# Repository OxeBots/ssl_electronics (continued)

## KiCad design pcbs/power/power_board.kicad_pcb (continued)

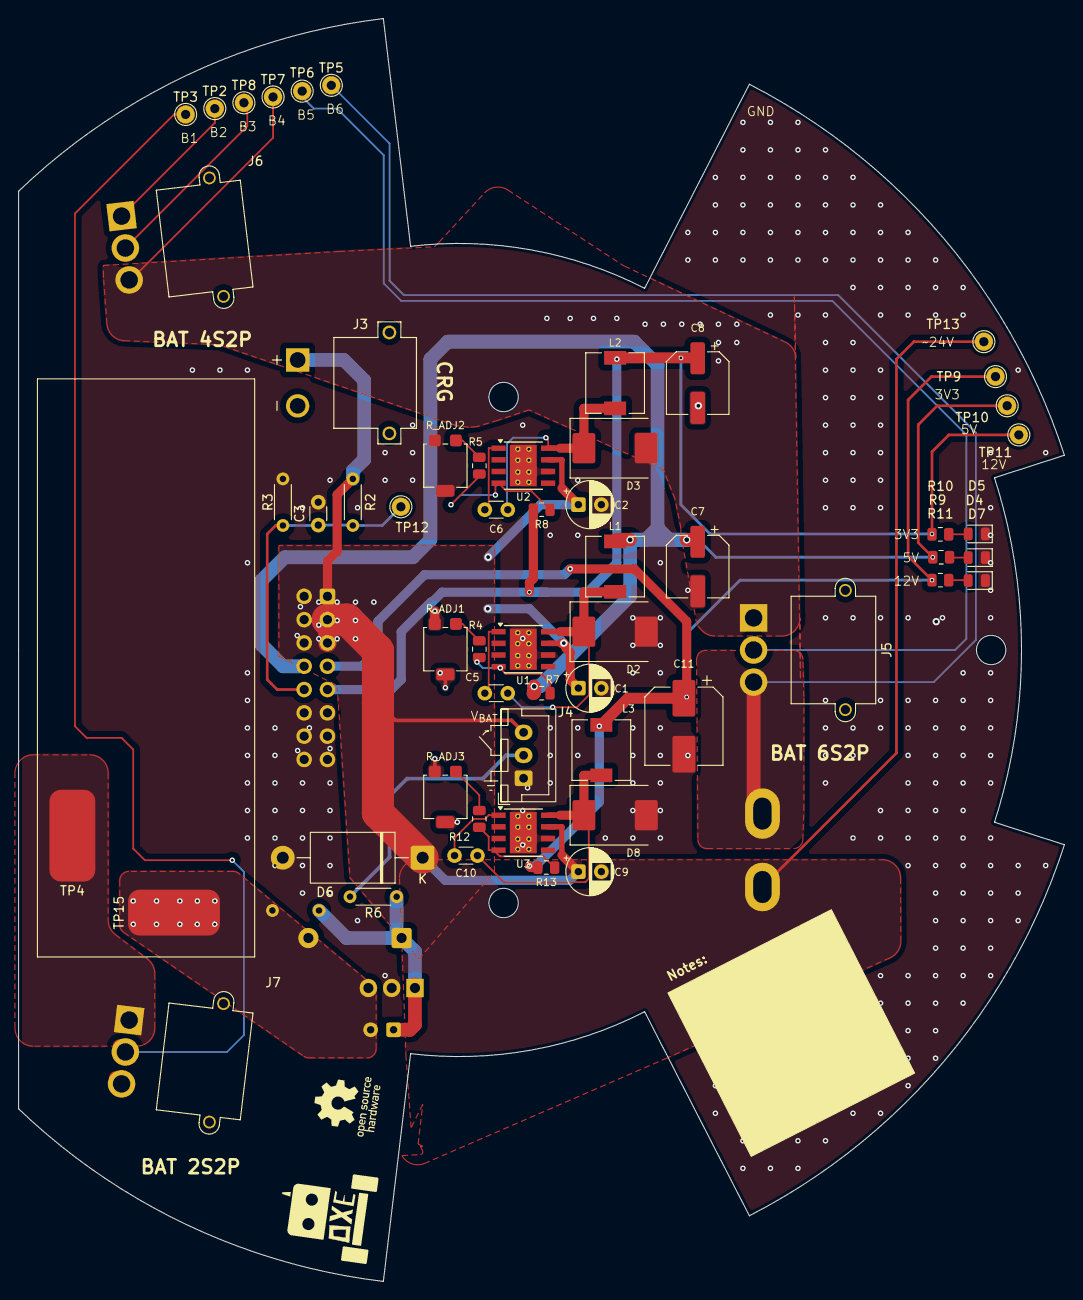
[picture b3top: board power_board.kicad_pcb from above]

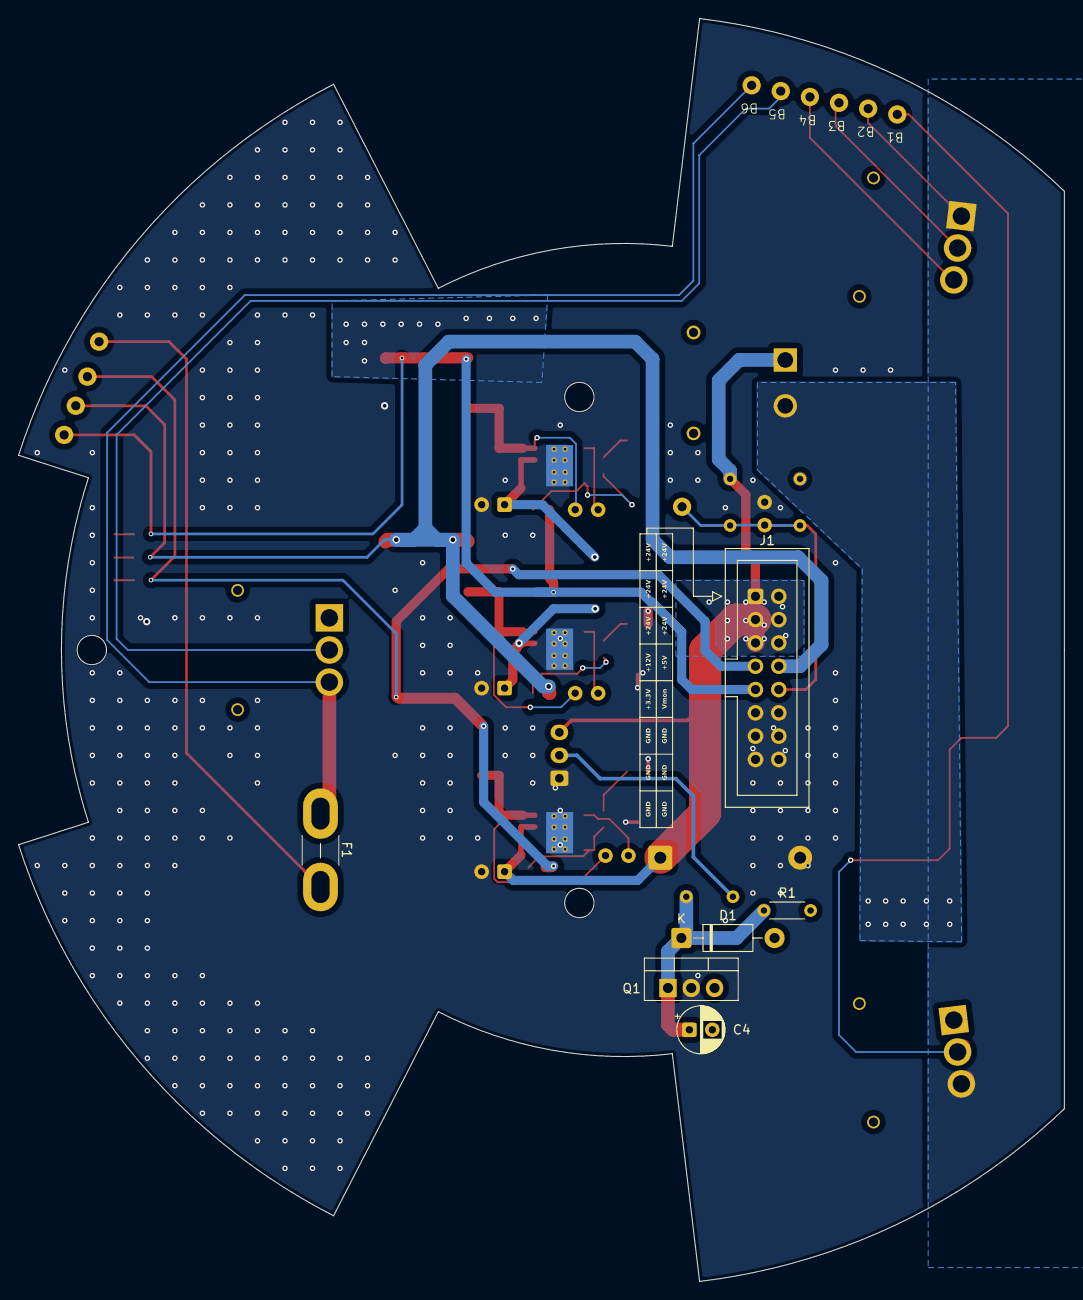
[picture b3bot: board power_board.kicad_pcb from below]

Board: 2 copper layers, 114.0 x 137.6 mm, 65 parts (6 on the bottom side), 31 nets.

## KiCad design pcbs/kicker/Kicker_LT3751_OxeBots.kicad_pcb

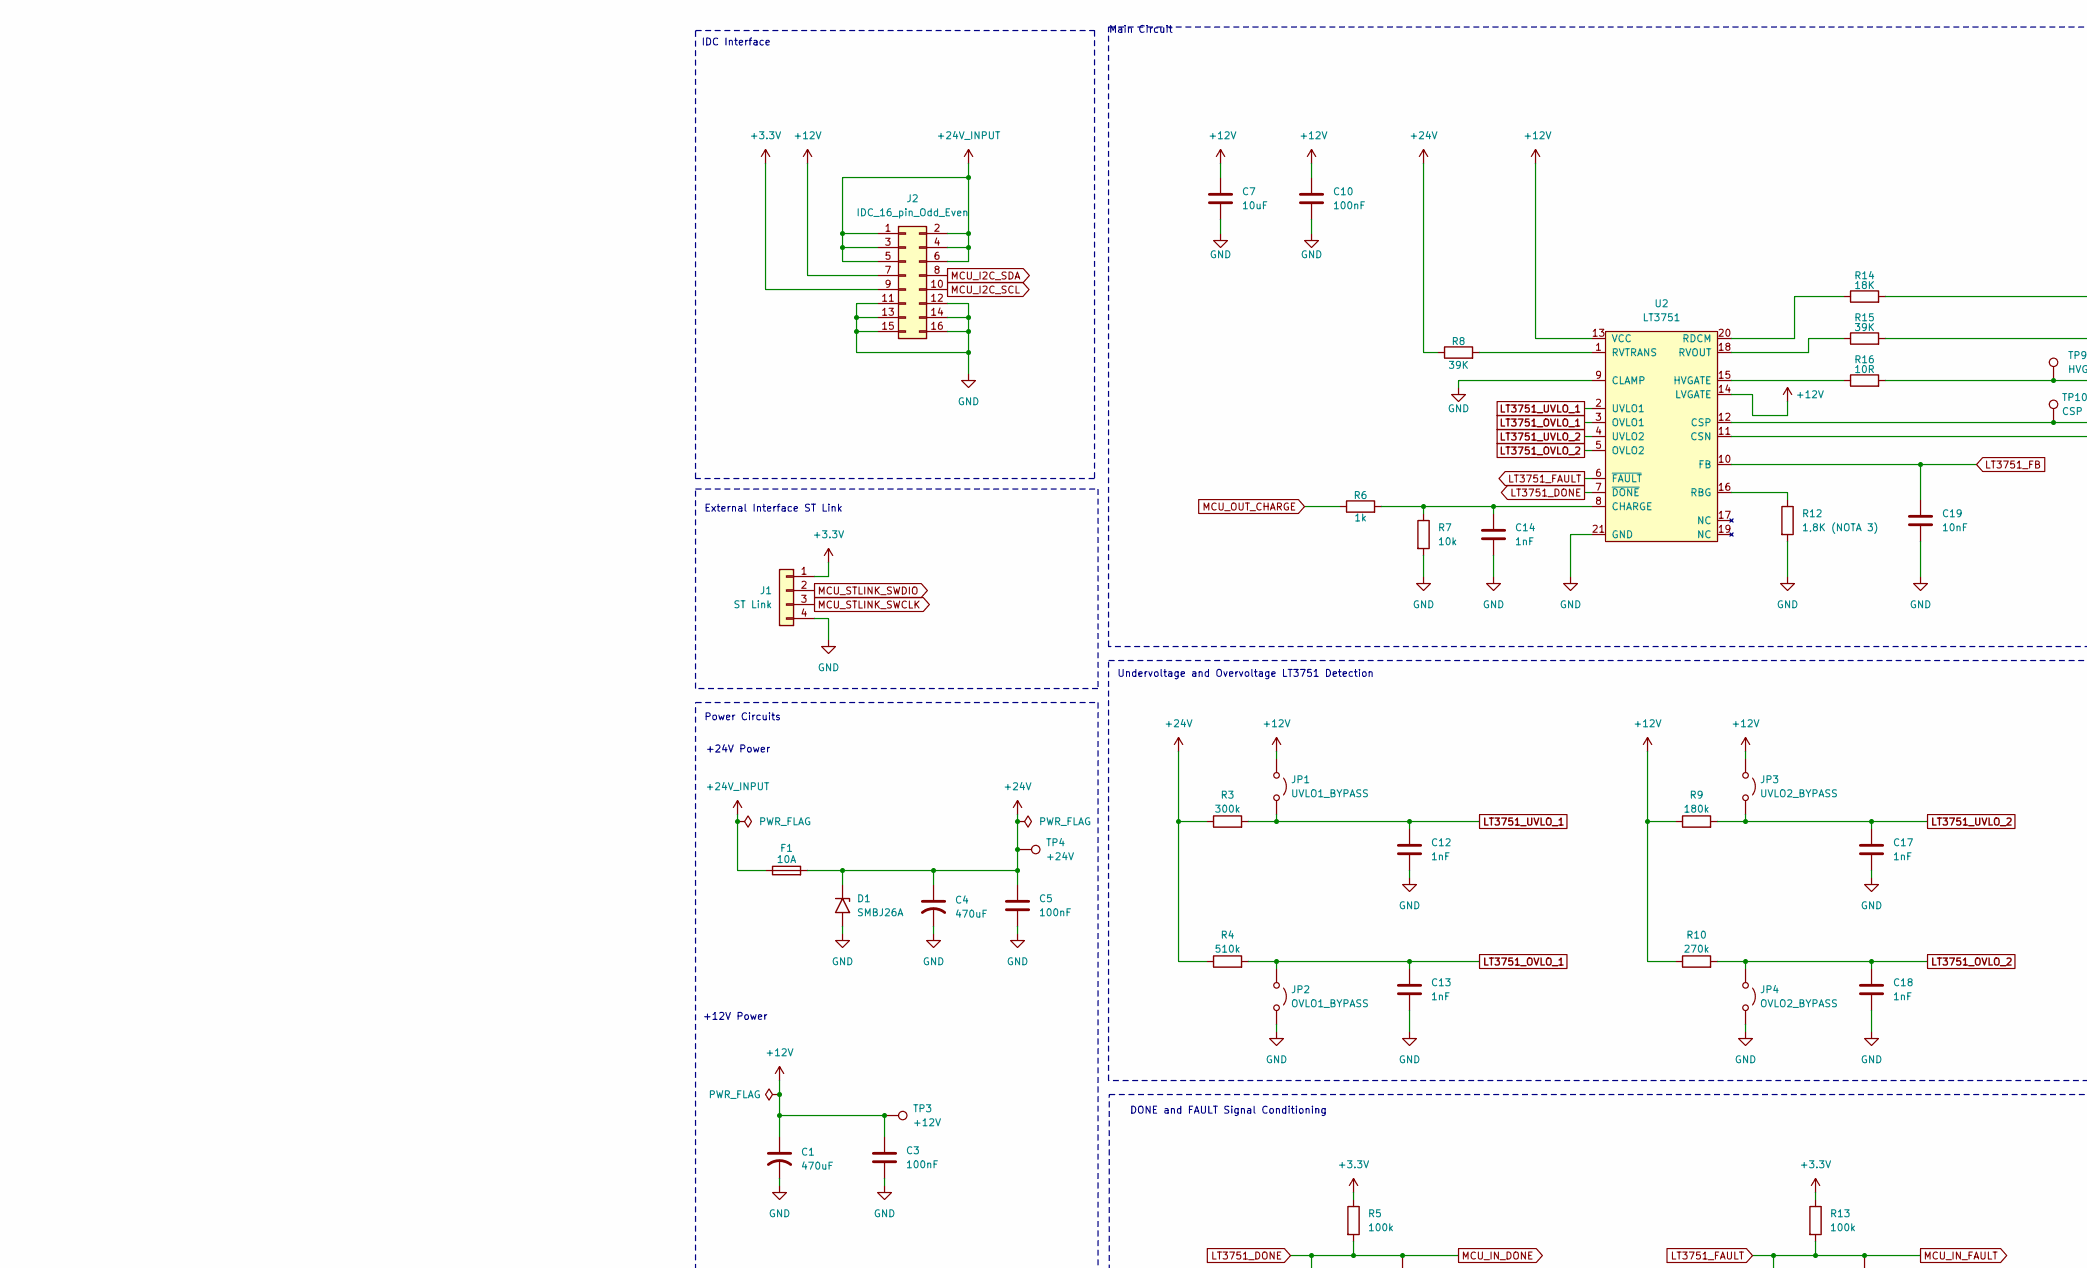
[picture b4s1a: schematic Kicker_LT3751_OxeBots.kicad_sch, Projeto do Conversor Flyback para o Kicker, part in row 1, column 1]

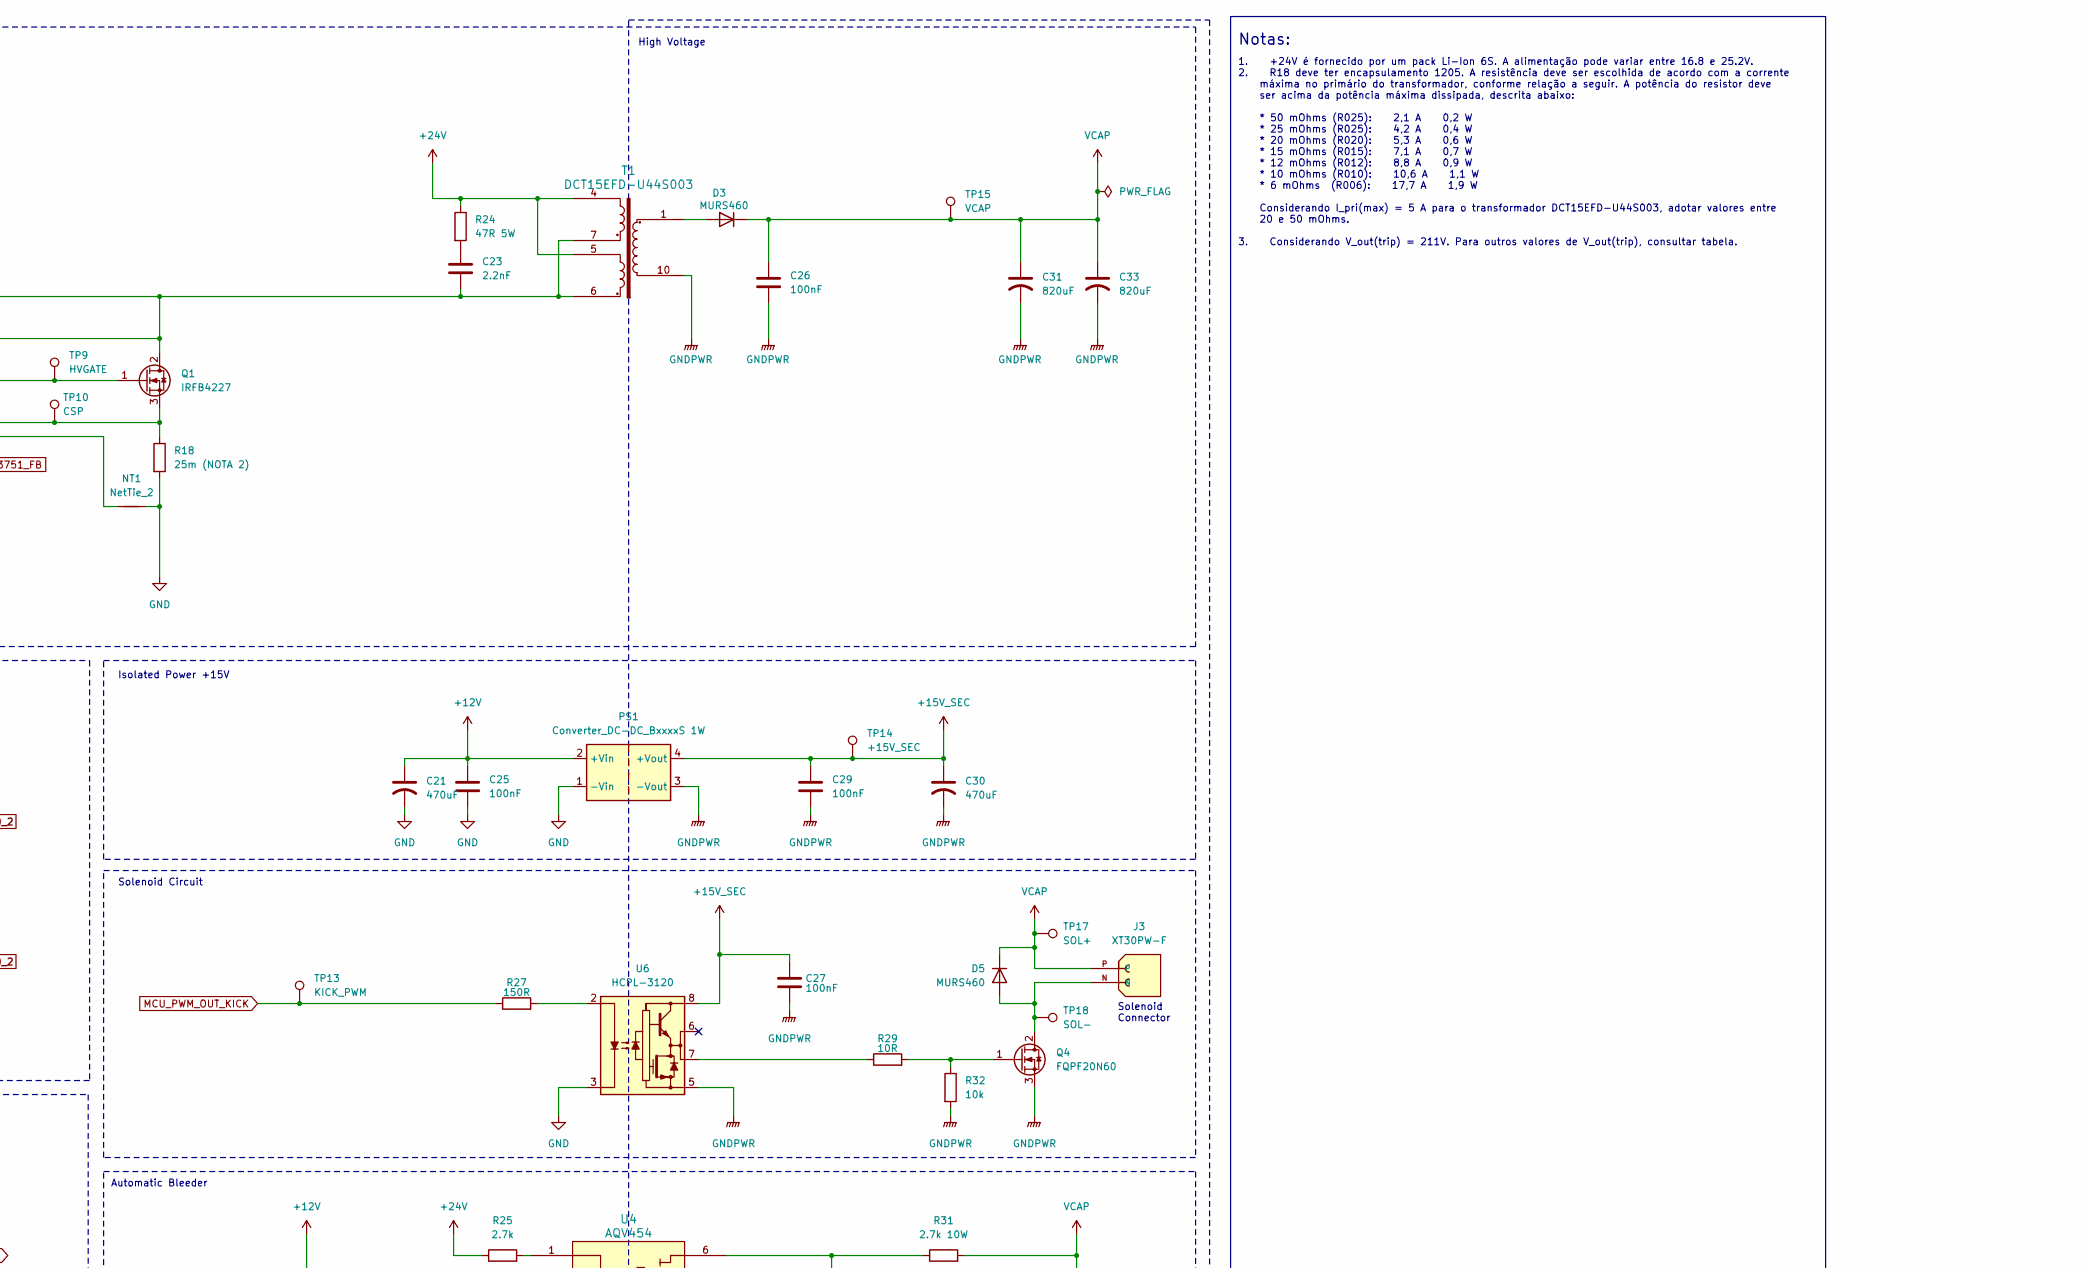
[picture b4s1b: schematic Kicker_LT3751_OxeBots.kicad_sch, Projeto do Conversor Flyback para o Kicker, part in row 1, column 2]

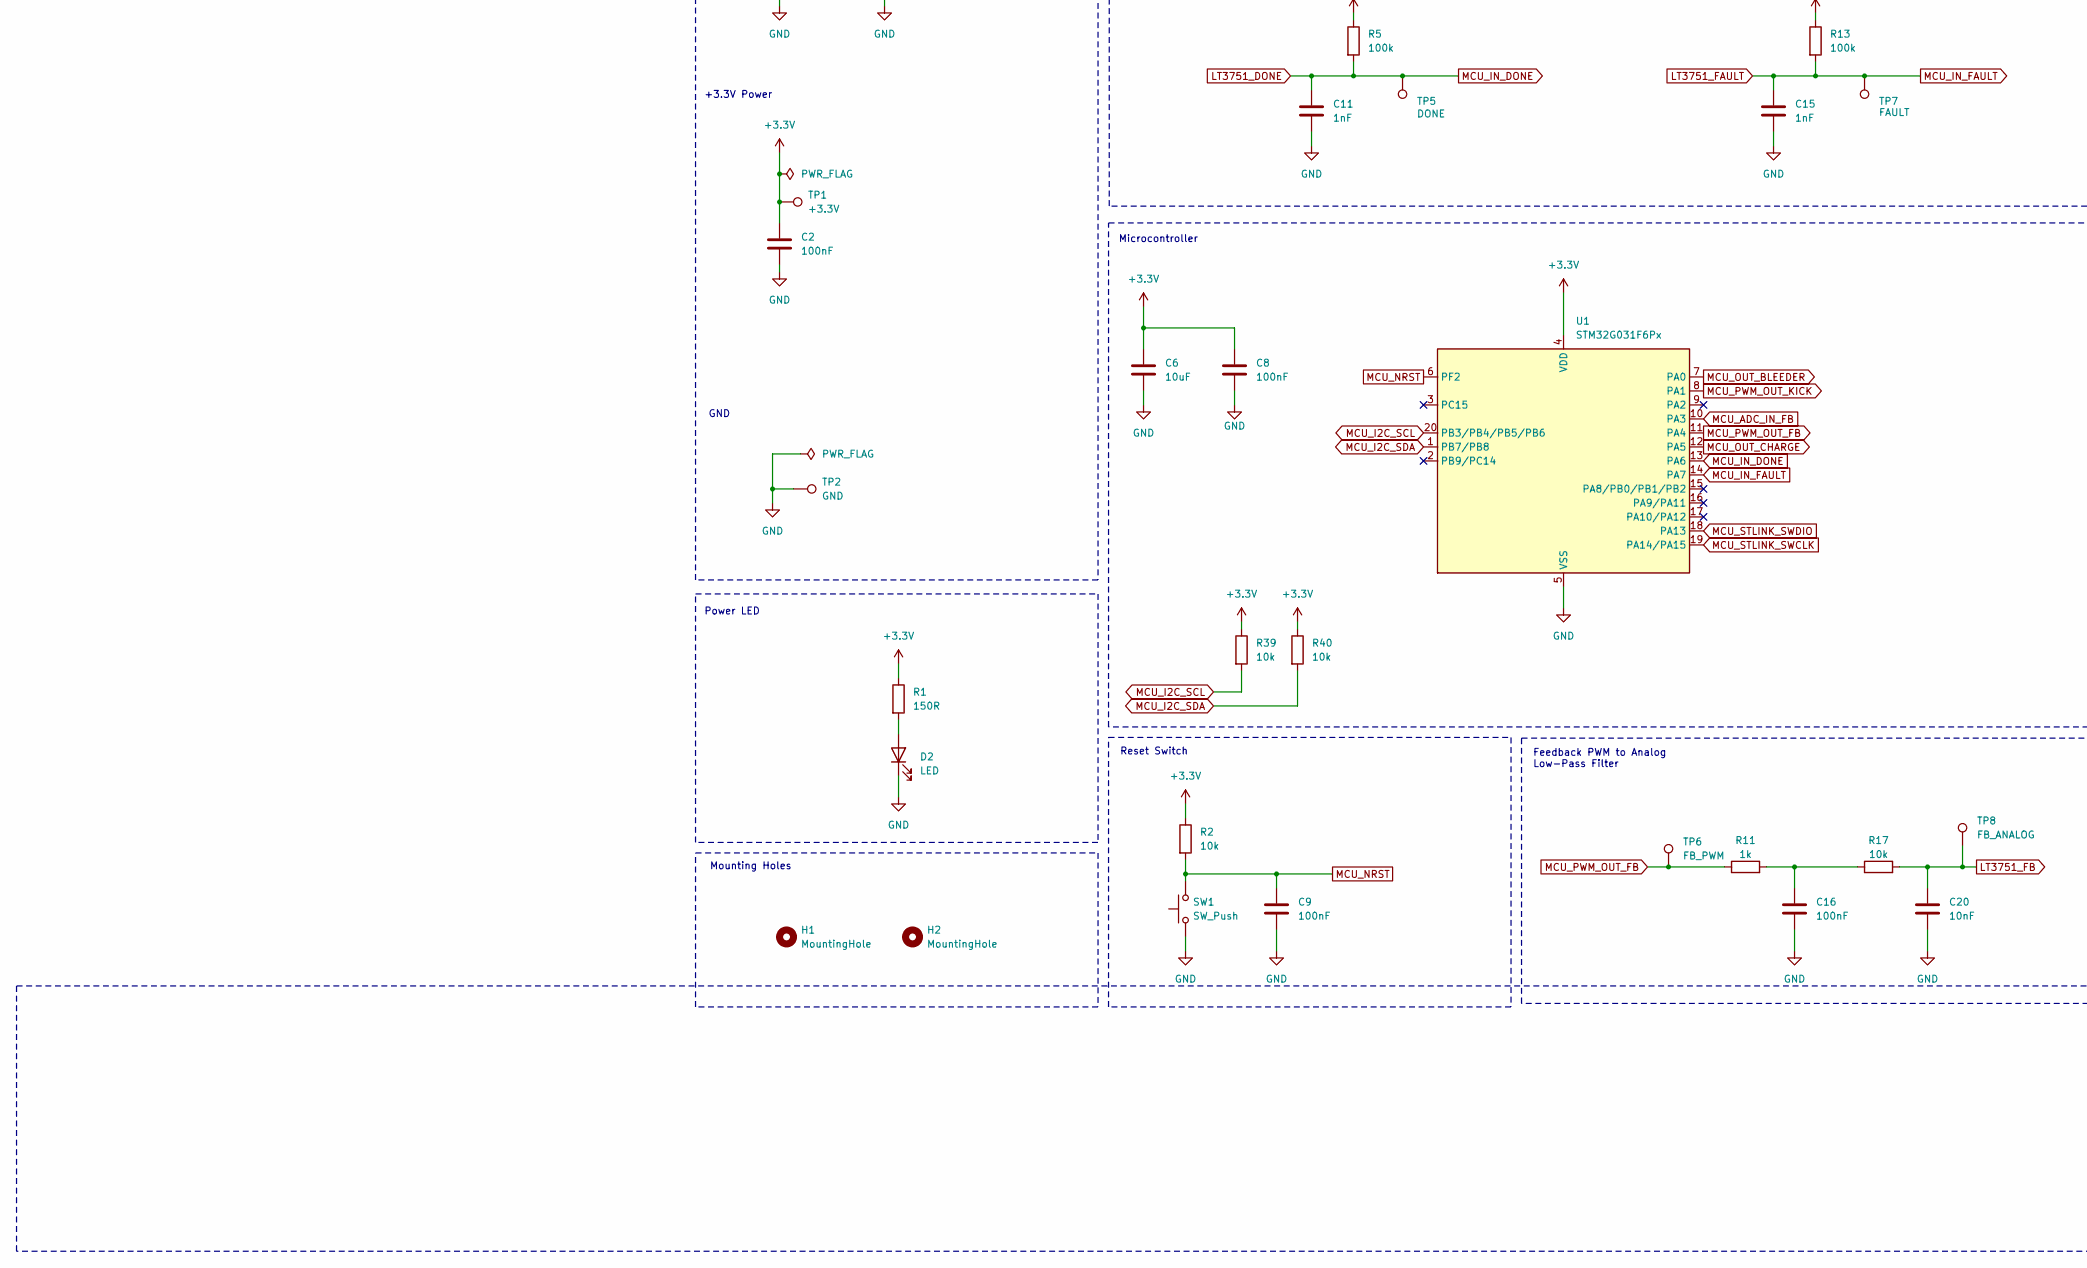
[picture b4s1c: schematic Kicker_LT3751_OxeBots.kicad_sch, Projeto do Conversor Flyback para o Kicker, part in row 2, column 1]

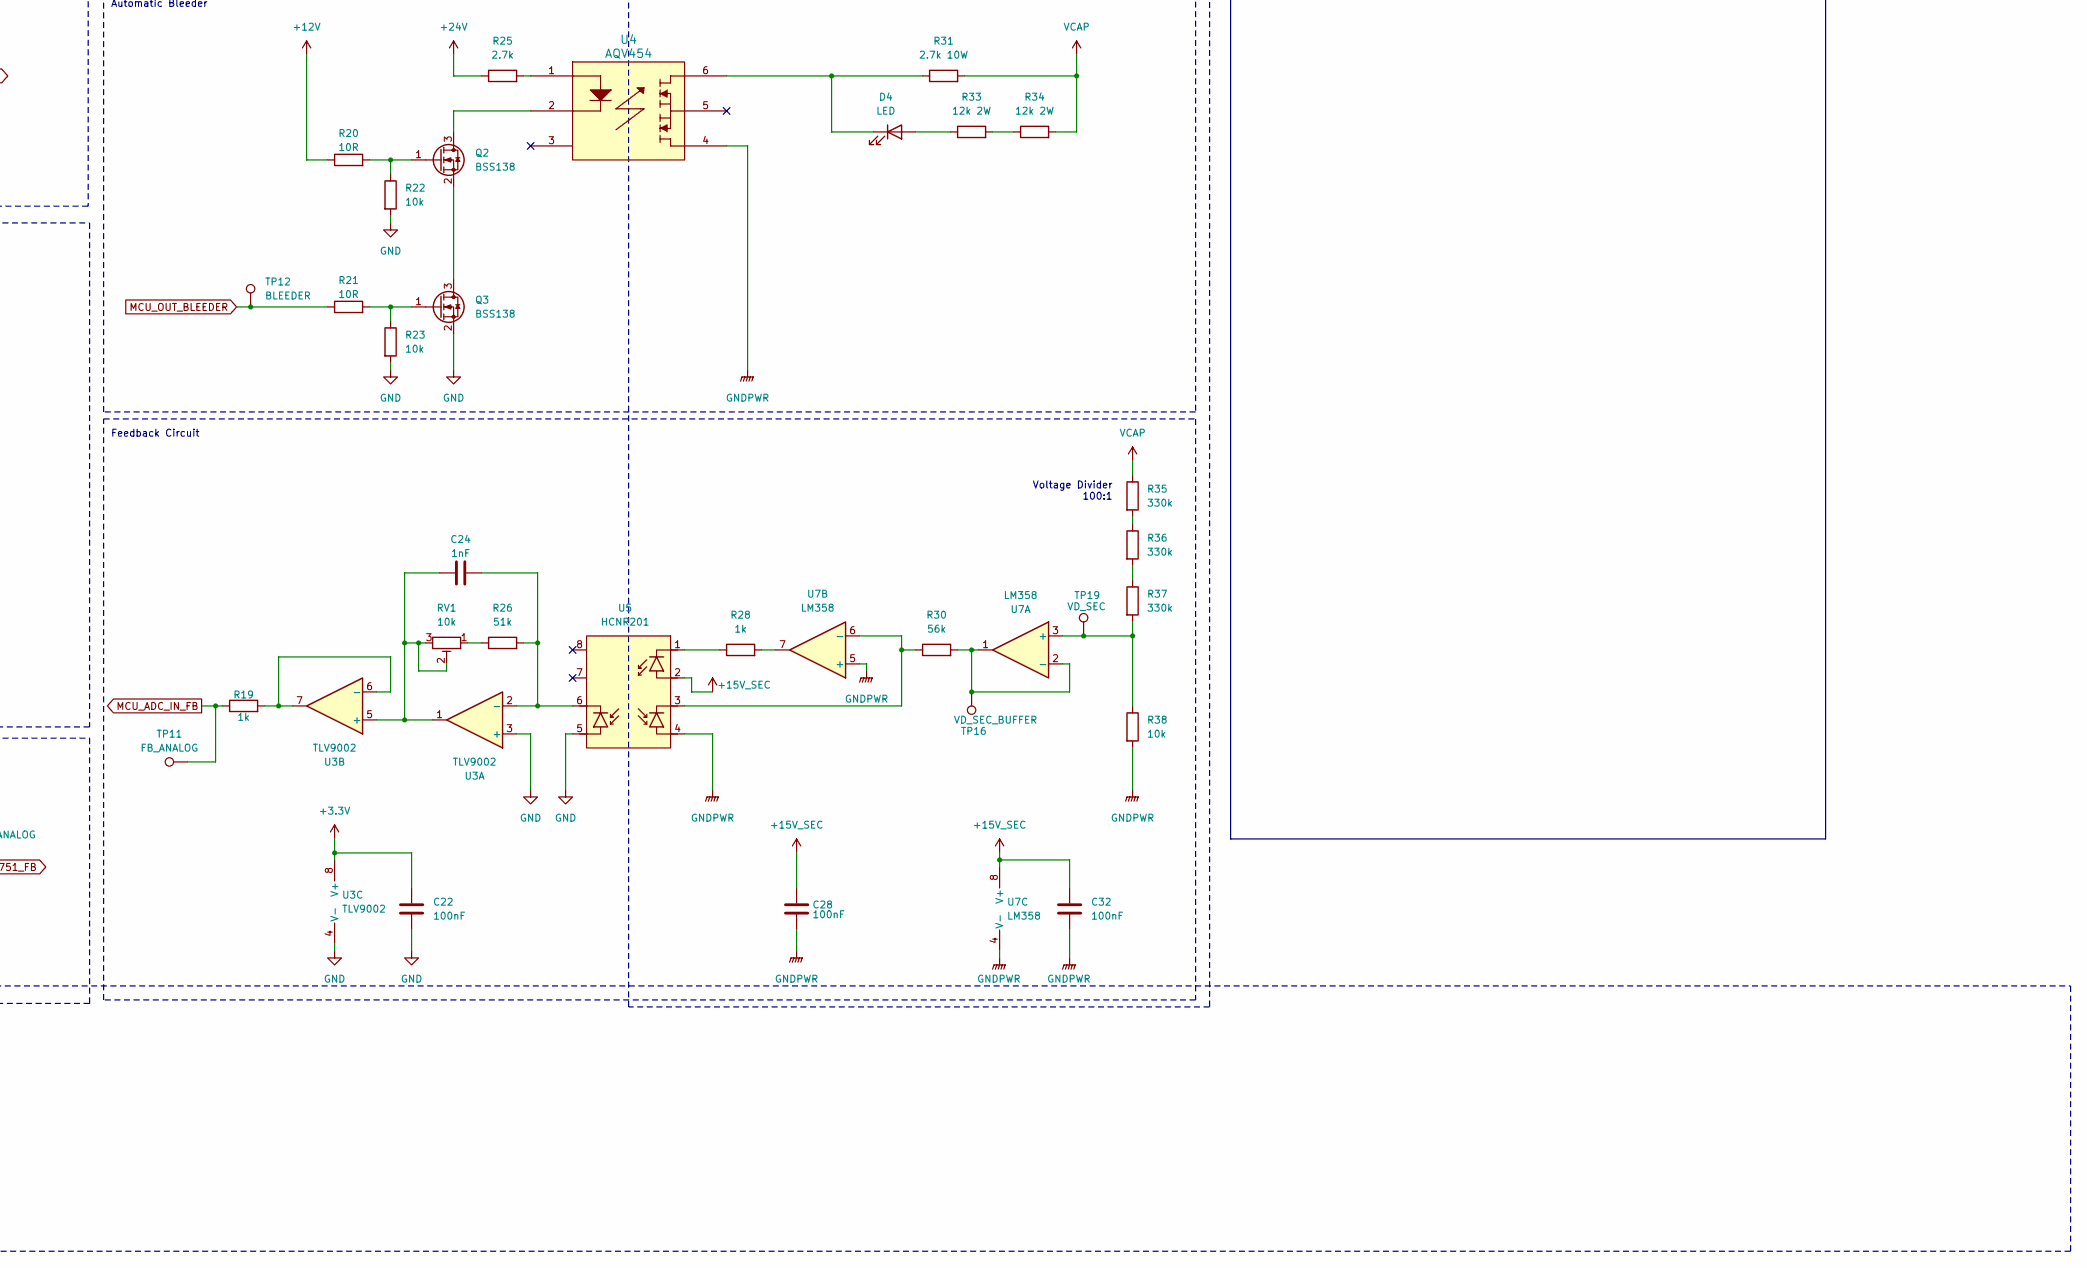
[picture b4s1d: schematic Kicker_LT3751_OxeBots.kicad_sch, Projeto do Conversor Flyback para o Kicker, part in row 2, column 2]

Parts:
C1, C21, C30: 470uF; CP_Elec_8x10
C2, C3, C5, C8, C9, C10, C16, C22, C25, C27, C28, C29, C32: 100nF; C_0805_2012Metric_Pad1.18x1.45mm_HandSolder
C4: 470uF; CP_Elec_10x12.5
C6, C7: 10uF; C_0805_2012Metric_Pad1.18x1.45mm_HandSolder
C11, C12, C13, C14, C15, C17, C18, C24: 1nF; C_0805_2012Metric_Pad1.18x1.45mm_HandSolder
C19, C20: 10nF; C_0805_2012Metric_Pad1.18x1.45mm_HandSolder
C23: 2.2nF; C_Rect_L10.3mm_W5.0mm_P7.50mm_MKS4
C26: 100nF; C_Rect_L13.0mm_W5.0mm_P10.00mm_FKS3_FKP3_MKS4
C31, C33: 820uF; CP_Radial_D30.0mm_P10.00mm_SnapIn
D1: SMBJ26A; D_SMB
D2: LED; LED_D3.0mm
D3, D5: MURS460; D_SMC_Handsoldering
D4: LED; LED_D5.0mm
F1: 10A; Fuse_Blade_Mini_directSolder
H1, H2: MountingHole; MountingHole_4.3mm_M4_Pad_Via
J1: ST Link; PinHeader_1x04_P2.54mm_Horizontal
J2: IDC_16_pin_Odd_Even; IDC-Header_2x08_P2.54mm_Vertical
J3: XT30PW-F; AMASS_XT30PW-M; PARTREV 1.2
JP1: UVLO1_BYPASS; SolderJumper-2_P1.3mm_Open_RoundedPad1.0x1.5mm
JP2: OVLO1_BYPASS; SolderJumper-2_P1.3mm_Open_RoundedPad1.0x1.5mm
JP3: UVLO2_BYPASS; SolderJumper-2_P1.3mm_Open_RoundedPad1.0x1.5mm
JP4: OVLO2_BYPASS; SolderJumper-2_P1.3mm_Open_RoundedPad1.0x1.5mm
NT1: NetTie_2; NetTie-2_SMD_Pad0.5mm
PS1: Converter_DC-DC_BxxxxS 1W; DC-DC_Converter_BxxxxS_1W
Q1: IRFB4227; TO-220-3_Horizontal_TabDown
Q2, Q3: BSS138; SOT-23
Q4: FQPF20N60; TO-220-3_Horizontal_TabDown
R1, R27: 150R; R_0805_2012Metric_Pad1.20x1.40mm_HandSolder
R2, R7, R17, R22, R23, R32, R38, R39, R40: 10k; R_0805_2012Metric_Pad1.20x1.40mm_HandSolder
R3: 300k; R_0805_2012Metric_Pad1.20x1.40mm_HandSolder
R4: 510k; R_0805_2012Metric_Pad1.20x1.40mm_HandSolder
R5, R13: 100k; R_0805_2012Metric_Pad1.20x1.40mm_HandSolder
R6, R11, R19, R28: 1k; R_0805_2012Metric_Pad1.20x1.40mm_HandSolder
R8, R15: 39K; R_0805_2012Metric_Pad1.20x1.40mm_HandSolder
R9: 180k; R_0805_2012Metric_Pad1.20x1.40mm_HandSolder
R10: 270k; R_0805_2012Metric_Pad1.20x1.40mm_HandSolder
R12: 1,8K (NOTA 3); R_0805_2012Metric_Pad1.20x1.40mm_HandSolder
R14: 18K; R_0805_2012Metric_Pad1.20x1.40mm_HandSolder
R16, R20, R21, R29: 10R; R_0805_2012Metric_Pad1.20x1.40mm_HandSolder
R18: 25m (NOTA 2); R_2512_6332Metric
R24: 47R 5W; R_Axial_DIN0617_L17.0mm_D6.0mm_P20.32mm_Horizontal
R25: 2.7k; R_2512_6332Metric_Pad1.40x3.35mm_HandSolder
R26: 51k; R_0805_2012Metric_Pad1.20x1.40mm_HandSolder
R30: 56k; R_0805_2012Metric_Pad1.20x1.40mm_HandSolder
R31: 2.7k 10W; Resistor_RX24_10W
R33, R34: 12k 2W; R_2512_6332Metric_Pad1.40x3.35mm_HandSolder
R35, R36, R37: 330k; R_0805_2012Metric_Pad1.20x1.40mm_HandSolder
RV1: 10k; trimpot_3362P
SW1: SW_Push; SW_SPST_SKQG_WithStem
T1: DCT15EFD-U44S003; TRANS_U44S003_TDK
TP1: +3.3V; TestPoint_Pad_D1.5mm
TP2: GND; TestPoint_Pad_D1.5mm
TP3: +12V; TestPoint_Pad_D1.5mm
TP4: +24V; TestPoint_Pad_D1.5mm
TP5: DONE; TestPoint_Pad_D1.5mm
TP6: FB_PWM; TestPoint_Pad_D1.5mm
TP7: FAULT; TestPoint_Pad_D1.5mm
TP8, TP11: FB_ANALOG; TestPoint_Pad_D1.5mm
TP9: HVGATE; TestPoint_Pad_D1.5mm
TP10: CSP; TestPoint_Pad_D1.5mm
TP12: BLEEDER; TestPoint_Pad_D1.5mm
TP13: KICK_PWM; TestPoint_Pad_D1.5mm
TP14: +15V_SEC; TestPoint_Pad_D1.5mm
TP15: VCAP; TestPoint_Pad_D1.5mm
TP16: VD_SEC_BUFFER; TestPoint_Pad_D1.5mm
TP17: SOL+; TestPoint_Pad_D1.5mm
TP18: SOL-; TestPoint_Pad_D1.5mm
TP19: VD_SEC; TestPoint_Pad_D1.5mm
U1: STM32G031F6Px; TSSOP-20_4.4x6.5mm_P0.65mm
U2: LT3751; Mouser 584-LT3751EFE#PBF
U3: TLV9002; SOIC-8_3.9x4.9mm_P1.27mm
U4: AQV454
U5: HCNR201; DIP-8_W10.16mm_LongPads
U6: HCPL-3120; DIP-8_W7.62mm_LongPads
U7: LM358; SOIC-8_3.9x4.9mm_P1.27mm

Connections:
+3.3V: C2.1, C6.1, C8.1, C22.1, J1.1, J2.9, R1.1, R2.1, R5.1, R13.1, R39.1, R40.1, TP1.1 (1_1), U1.4 (VDD), U3.8 (V+)
+12V: C1.1, C3.1, C7.1, C10.1, C21.1, C25.1, J2.7, JP1.1 (A), JP3.1 (A), PS1.2 (+Vin), R9.1, R10.1, R20.1, TP3.1 (1_1), U2.13 (VCC), U2.14 (LVGATE)
+15V_SEC: C27.1, C28.1, C29.1, C30.1, C32.1, PS1.4 (+Vout), TP14.1 (1_1), U5.2, U6.8 (VCC), U7.8 (V+)
+24V: C4.1, C5.1, D1.1 (A1), F1.2, R3.1, R4.1, R8.1, R24.1, R25.1, T1.4, T1.5, TP4.1 (1_1)
+24V_INPUT: F1.1, J2.1, J2.2, J2.3, J2.4, J2.5, J2.6
GND: C1.2, C2.2, C3.2, C4.2, C5.2, C6.2, C7.2, C8.2, C9.2, C10.2, C11.2, C12.2, C13.2, C14.2, C15.2, C16.2, C17.2, C18.2, C19.2, C20.2, C21.2, C22.2, C25.2, D1.2 (A2), D2.1 (K), J1.4, J2.11, J2.12, J2.13, J2.14, J2.15, J2.16, JP2.2 (B), JP4.2 (B), NT1.2, PS1.1 (-Vin), Q3.2 (S), R7.2, R12.2, R18.2, R22.2, R23.2, SW1.1, TP2.1 (1_1), U1.5 (VSS), U2.9 (CLAMP), U2.21 (GND), U3.3 (+), U3.4 (V-), U5.5, U6.3 (C)
GNDPWR: C26.2, C27.2, C28.2, C29.2, C30.2, C31.2, C32.2, C33.2, PS1.3 (-Vout), Q4.3 (S), R32.2, R38.2, T1.10, U4.4, U5.4, U6.5 (VEE), U7.4 (V-), U7.5 (+)
LT3751_DONE: C11.1, R5.2, TP5.1 (1_1), U1.13 (PA6), U2.7 (~DONE)
LT3751_FAULT: C15.1, R13.2, TP7.1 (1_1), U1.14 (PA7), U2.6 (~FAULT)
LT3751_FB: C19.1, C20.1, R17.2, TP8.1 (1_1), U2.10 (FB)
LT3751_OVLO_1: C13.1, JP2.1 (A), R4.2, U2.3 (OVLO1)
LT3751_OVLO_2: C18.1, JP4.1 (A), R10.2, U2.5 (OVLO2)
LT3751_UVLO_1: C12.1, JP1.2 (B), R3.2, U2.2 (UVLO1)
LT3751_UVLO_2: C17.1, JP3.2 (B), R9.2, U2.4 (UVLO2)
MCU_ADC_IN_FB: R19.1, TP11.1 (1_1), U1.10 (PA3)
MCU_I2C_SCL: J2.10, R39.2, U1.20 (PB3/PB4/PB5/PB6)
MCU_I2C_SDA: J2.8, R40.2, U1.1 (PB7/PB8)
MCU_NRST: C9.1, R2.2, SW1.2, U1.6 (PF2)
MCU_OUT_BLEEDER: R21.1, TP12.1 (1_1), U1.7 (PA0)
MCU_OUT_CHARGE: R6.1, U1.12 (PA5)
MCU_PWM_OUT_FB: R11.1, TP6.1 (1_1), U1.11 (PA4)
MCU_PWM_OUT_KICK: R27.1, TP13.1 (1_1), U1.8 (PA1)
MCU_STLINK_SWCLK: J1.3, U1.19 (PA14/PA15)
MCU_STLINK_SWDIO: J1.2, U1.18 (PA13)
unnamed: C16.1, R11.2, R17.1
unnamed: C23.1, R24.2
unnamed: D2.2 (A), R1.2
unnamed: D3.2 (A), T1.1
unnamed: D4.2 (A), R33.1
unnamed: D4.1 (K), R31.1, U4.6
unnamed: D5.2 (A), J3.N, Q4.2 (D), TP18.1 (1_1)
unnamed: C23.2, Q1.2 (D), R14.2, R15.2, T1.6, T1.7
unnamed: Q1.1 (G), R16.2, TP9.1 (1_1)
unnamed: Q1.3 (S), R18.1, TP10.1 (1_1), U2.12 (CSP)
unnamed: Q2.3 (D), U4.2
unnamed: Q2.1 (G), R20.2, R22.1
unnamed: Q2.2 (S), Q3.3 (D)
unnamed: Q3.1 (G), R21.2, R23.1
unnamed: Q4.1 (G), R29.2, R32.1
unnamed: R25.2, U4.1
unnamed: R26.1, RV1.1
unnamed: R28.1, U5.1
unnamed: R28.2, U7.7
unnamed: R29.1, U6.7 (VO)
unnamed: R33.2, R34.1
unnamed: R35.2, R36.1
unnamed: R36.2, R37.1
unnamed: C14.1, R6.2, R7.1, U2.8 (CHARGE)
unnamed: NT1.1, U2.11 (CSN)
unnamed: R16.1, U2.15 (HVGATE)
unnamed: R12.1, U2.16 (RBG)
unnamed: R14.1, U2.20 (RDCM)
unnamed: R15.1, U2.18 (RVOUT)
unnamed: R8.2, U2.1 (RVTRANS)
unnamed: C24.1, R26.2, U3.2 (-), U5.6
unnamed: C24.2, RV1.2, RV1.3, U3.1, U3.5 (+)
unnamed: R19.2, U3.6 (-), U3.7
unnamed: R27.2, U6.2 (A)
unnamed: R37.2, R38.1, TP19.1 (1_1), U7.3 (+)
unnamed: R30.2, TP16.1 (1_1), U7.1, U7.2 (-)
unnamed: R30.1, U5.3, U7.6 (-)
VCAP: C26.1, C31.1, C33.1, D3.1 (K), D5.1 (K), J3.P, R31.2, R34.2, R35.1, TP15.1 (1_1), TP17.1 (1_1)

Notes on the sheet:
Power Circuits
High Voltage
Isolated Power +15V
IDC Interface
Notas:
Automatic Bleeder
Power LED
Feedback Circuit
Microcontroller
+24V Power
DONE and FAULT Signal Conditioning
Main Circuit
Voltage Divider 100:1
Solenoid Circuit
+12V Power
Mounting Holes
+3.3V Power
Reset Switch
GND
1. +24V é fornecido por um pack Li-Ion 6S. A alimentação pode variar entre 16.8 e 25.2V. 2. R18 deve ter encapsulamento 1205. A resistência deve ser escolhida de acordo com a corrente máxima no primário do transformador, conforme relação a seguir. A potência do resistor deve ser acima da potência m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
Solenoid Connector
Feedback PWM to Analog Low-Pass Filter
Undervoltage and Overvoltage LT3751 Detection
External Interface ST Link

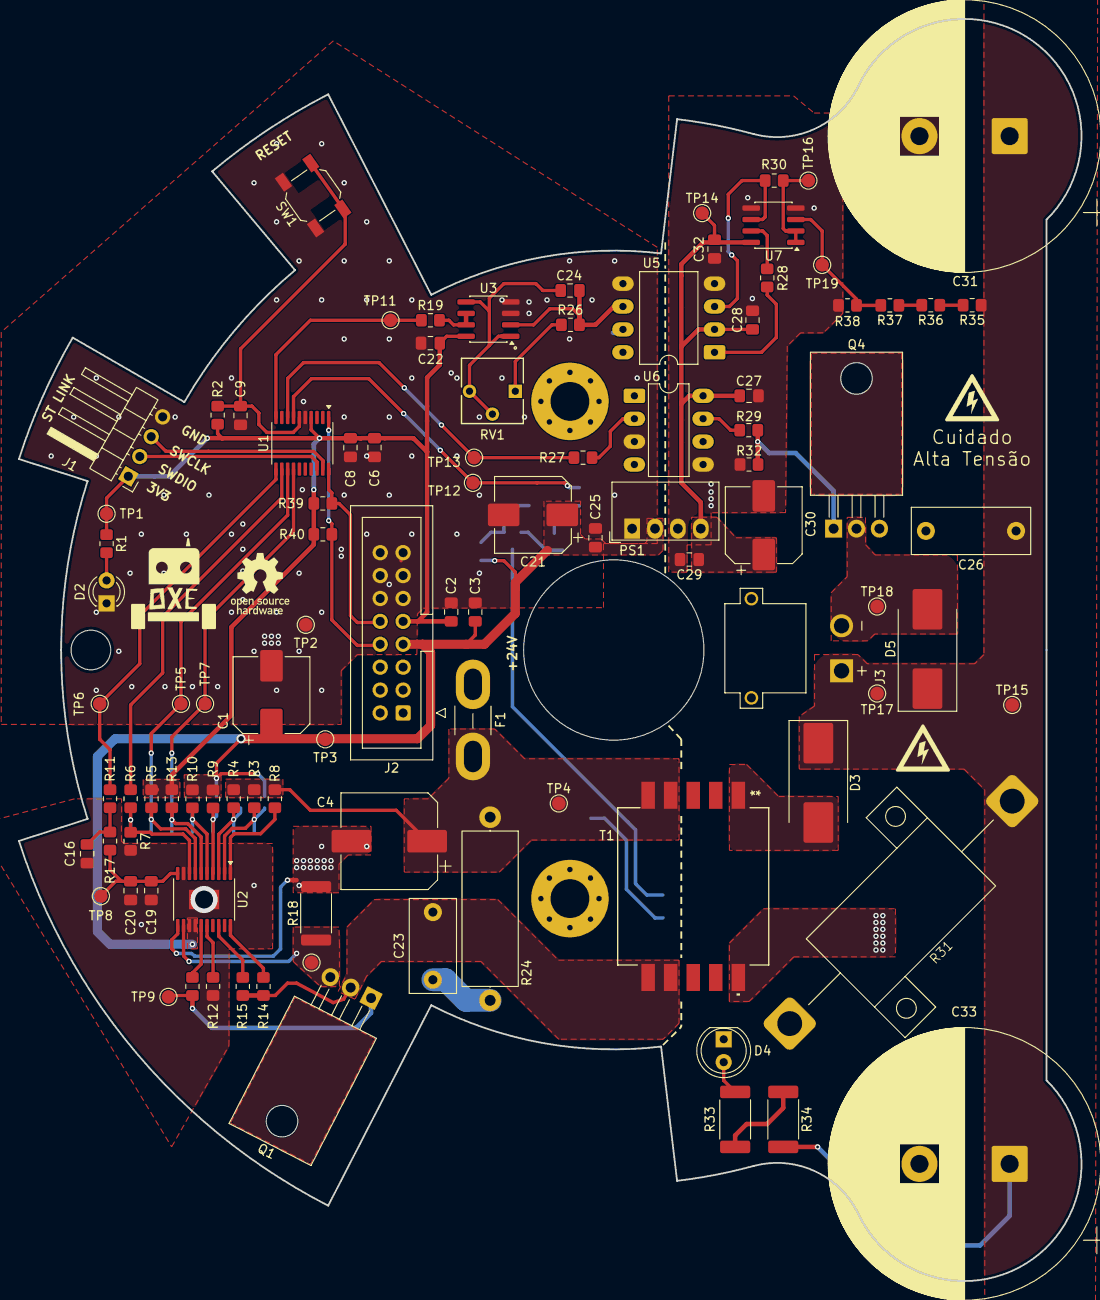
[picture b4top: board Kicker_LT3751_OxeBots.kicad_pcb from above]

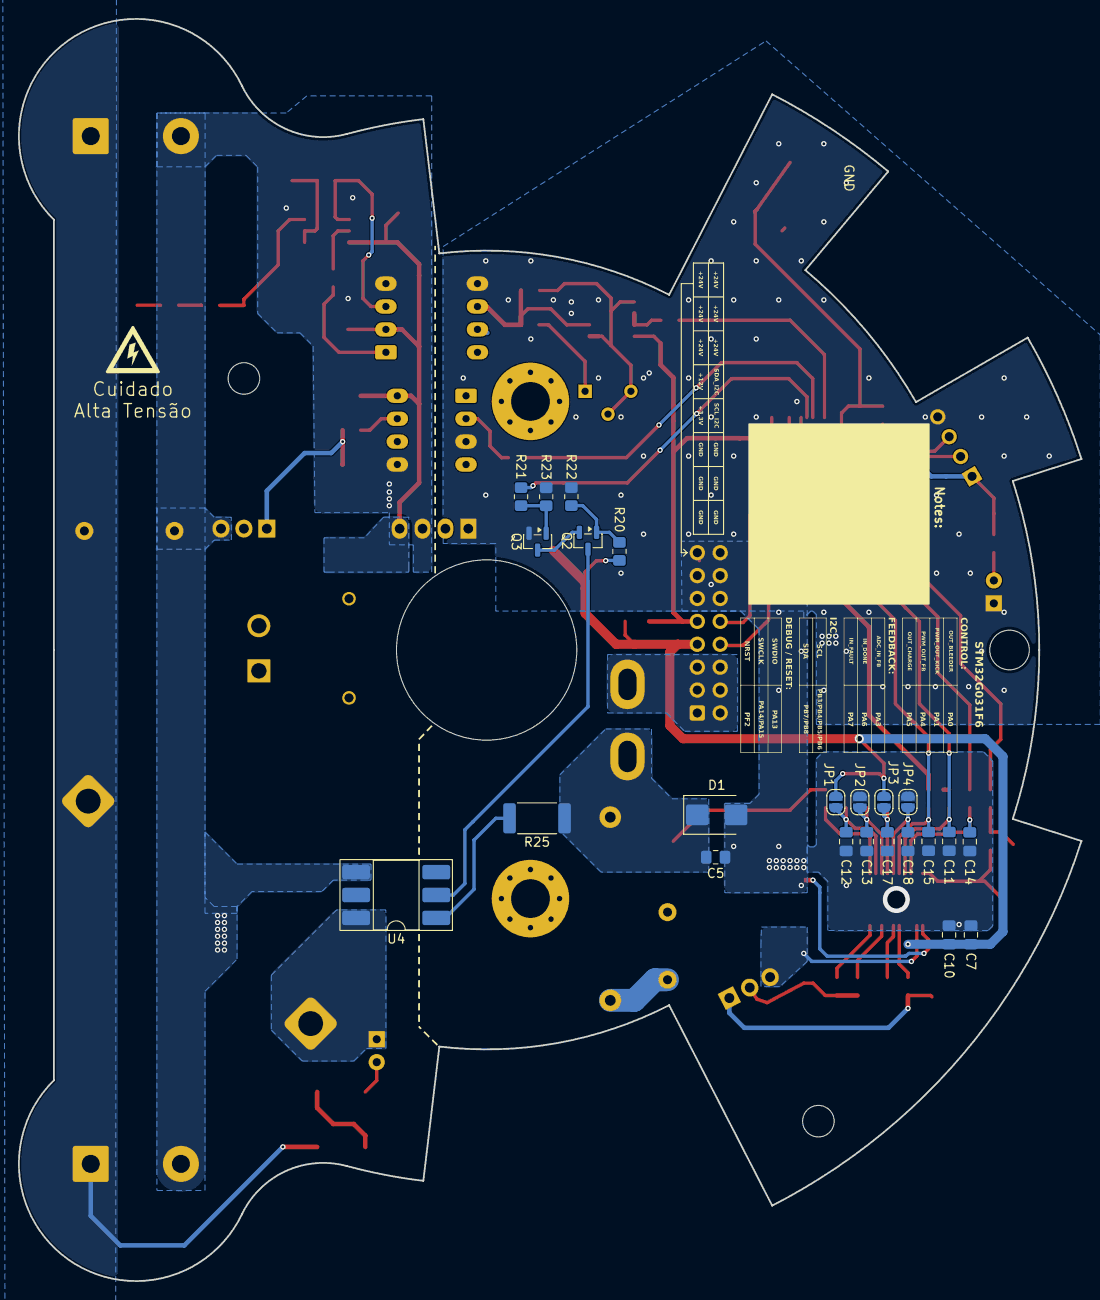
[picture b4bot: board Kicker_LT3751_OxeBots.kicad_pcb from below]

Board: 2 copper layers, 117.9 x 140.0 mm, 123 parts (23 on the bottom side), 62 nets.
